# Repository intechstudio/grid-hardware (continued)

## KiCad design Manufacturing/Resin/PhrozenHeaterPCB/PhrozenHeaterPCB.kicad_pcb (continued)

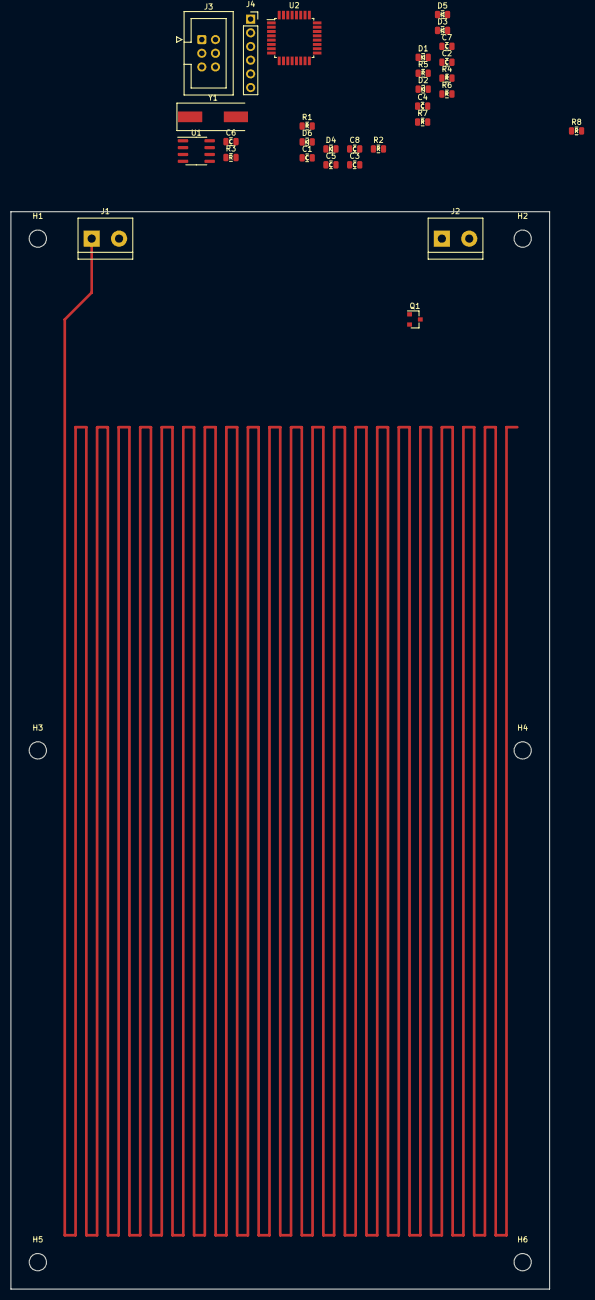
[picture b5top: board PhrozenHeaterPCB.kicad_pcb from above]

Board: 2 copper layers, 100.0 x 200.0 mm, 36 parts (0 on the bottom side), 26 nets.
